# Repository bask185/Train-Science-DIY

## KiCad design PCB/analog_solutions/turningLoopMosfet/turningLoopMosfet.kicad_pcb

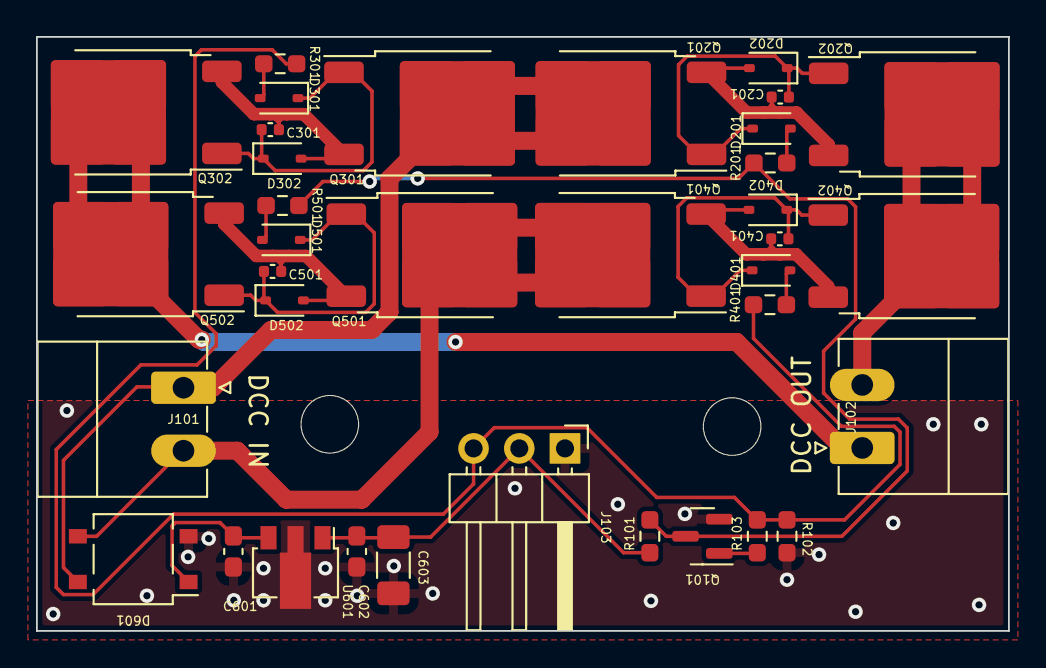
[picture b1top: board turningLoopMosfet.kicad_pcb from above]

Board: 2 copper layers, 54.0 x 33.0 mm, 36 parts (0 on the bottom side), 22 nets.

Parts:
C201, C301, C401, C501: 100nF; C_0402_1005Metric
C601: 330nF; C_0603_1608Metric_Pad1.08x0.95mm_HandSolder
C602: 100nF; C_0603_1608Metric_Pad1.08x0.95mm_HandSolder
C603: 100uF; C_1206_3216Metric_Pad1.33x1.80mm_HandSolder
D201, D202, D301, D302, D401, D402, D501, D502: 1N4148WS; D_SOD-323
D601: MB10S; TO-269AA
J101, J102: Screw_Terminal_01x02; PhoenixContact_MC_1,5_2-G-3.5_1x02_P3.50mm_Horizontal
J103: Conn_01x03_Pin; PinHeader_1x03_P2.54mm_Horizontal
Q101: NPN_TOR; SOT-23
Q201, Q202, Q301, Q302, Q401, Q402, Q501, Q502: MDD50N03D; TO-252-2
R101, R102: 22k; R_0603_smalltext
R103: 2k2; R_0603_smalltext
R201, R301, R401, R501: 100R; R_0603_smalltext
U601: L78L12_SOT89; SOT-89-3

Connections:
+12V: C602.1, C603.1, J103.2, R101.1, U601.1 (OUT)
/DCC_IN_A: D601.3, J101.2, Q401.2 (D), Q501.2 (D)
/DCC_IN_B: D601.4, J101.1, Q201.2 (D), Q301.2 (D)
/DCC_OUT_A: J102.1, Q302.2 (D), Q502.2 (D)
/DCC_OUT_B: J102.2, Q202.2 (D), Q402.2 (D)
/Mosfets2/GATE: Q101.3 (C), R101.2, R201.1, R501.1
/Vo: J103.3, R102.1, R103.2, R301.1, R401.1
GND: C601.2, C602.2, C603.2, D601.2 (-), J103.1, Q101.2 (E), R102.2, U601.2 (GND)
unnamed: D201.2 (A), R201.2
unnamed: C201.2, D201.1 (K), D202.1 (K), Q201.1 (G), Q202.1 (G)
unnamed: C201.1, D202.2 (A), Q201.3 (S), Q202.3 (S)
unnamed: D301.2 (A), R301.2
unnamed: C301.2, D301.1 (K), D302.1 (K), Q301.1 (G), Q302.1 (G)
unnamed: C301.1, D302.2 (A), Q301.3 (S), Q302.3 (S)
unnamed: D401.2 (A), R401.2
unnamed: C401.2, D401.1 (K), D402.1 (K), Q401.1 (G), Q402.1 (G)
unnamed: C401.1, D402.2 (A), Q401.3 (S), Q402.3 (S)
unnamed: D501.2 (A), R501.2
unnamed: C501.2, D501.1 (K), D502.1 (K), Q501.1 (G), Q502.1 (G)
unnamed: C501.1, D502.2 (A), Q501.3 (S), Q502.3 (S)
unnamed: Q101.1 (B), R103.1
VCC: C601.1, D601.1 (+), U601.3 (IN)

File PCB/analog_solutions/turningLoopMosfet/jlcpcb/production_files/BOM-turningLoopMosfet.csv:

Comment,Designator,Footprint,LCSC
100nF,C602,C_0603_1608Metric_Pad1.08x0.95mm_HandSolder,C14663
100uF,C603,C_1206_3216Metric_Pad1.33x1.80mm_HandSolder,C15008
330nF,C601,C_0603_1608Metric_Pad1.08x0.95mm_HandSolder,C1615
1N4148WS,"D201,D202,D301,D302,D401,D402,D501,D502",D_SOD-323,C2128
NPN_TOR,Q101,SOT-23,C2145
100R,"R201,R301,R401,R501",R_0603_smalltext,C22775
MB10S,D601,TO-269AA,C2488
100nF,"C201,C301,C401,C501",C_0402_1005Metric,C307331
22k,"R101,R102",R_0603_smalltext,C31850
2k2,R103,R_0603_smalltext,C4190
MDD50N03D,"Q201,Q202,Q301,Q302,Q401,Q402,Q501,Q502",TO-252-2,C5357578
L78L12_SOT89,U601,SOT-89-3,C75501

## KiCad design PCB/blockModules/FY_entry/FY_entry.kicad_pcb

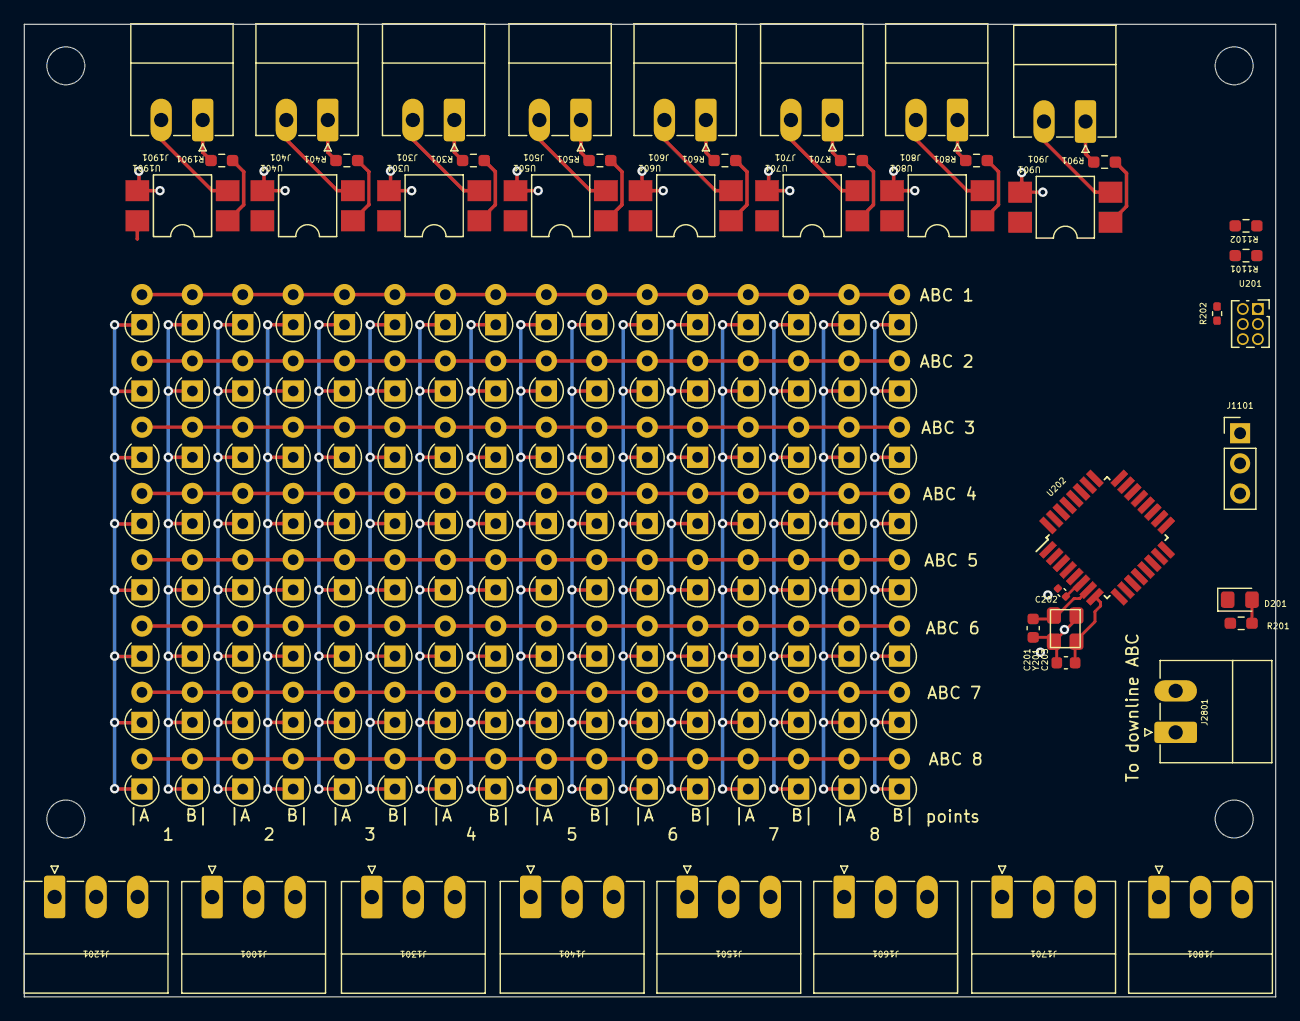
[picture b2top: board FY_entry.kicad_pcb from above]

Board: 2 copper layers, 105.5 x 82.0 mm, 173 parts (0 on the bottom side), 67 nets.

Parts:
C201, C203: 12pF; C_0603_1608Metric
C202: 100nF; C_0402_1005Metric
D201: LED; LED_0805_2012Metric_Pad1.15x1.40mm_HandSolder
D1901, D1902, D1903, D1904, D1905, D1906, D1907, D1908, D1909, D1910, D1911, D1912, D1913, D1914, D1915, D1916, D2101, D2102, D2103, D2104, D2105, D2106, D2107, D2108, D2109, D2110, D2111, D2112, D2113, D2114, D2115, D2116, D2201, D2202, D2203, D2204, D2205, D2206, D2207, D2208, D2209, D2210, D2211, D2212, D2213, D2214, D2215, D2216, D2301, D2302, D2303, D2304, D2305, D2306, D2307, D2308, D2309, D2310, D2311, D2312, D2313, D2314, D2315, D2316, D2401, D2402, D2403, D2404, D2405, D2406, D2407, D2408, D2409, D2410, D2411, D2412, D2413, D2414, D2415, D2416, D2501, D2502, D2503, D2504, D2505, D2506, D2507, D2508, D2509, D2510, D2511, D2512, D2513, D2514, D2515, D2516, D2601, D2602, D2603, D2604, D2605, D2606, D2607, D2608, D2609, D2610, D2611, D2612, D2613, D2614, D2615, D2616, D2701, D2702, D2703, D2704, D2705, D2706, D2707, D2708, D2709, D2710, D2711, D2712, D2713, D2714, D2715, D2716: D; D_A-405_P2.54mm_Vertical_AnodeUp
J301, J401, J501, J601, J701, J801, J901, J1901, J2801: Screw_Terminal_01x02; PhoenixContact_MC_1,5_2-G-3.5_1x02_P3.50mm_Horizontal
J1001, J1201, J1301, J1401, J1501, J1601, J1701, J1801: Screw_Terminal_01x03; PhoenixContact_MC_1,5_3-G-3.5_1x03_P3.50mm_Horizontal
J1101: Conn_01x03; PinHeader_1x03_P2.54mm_Vertical
R201: 6k2; R_0603_1608Metric_Pad0.98x0.95mm_HandSolder
R202: 10k; R_0402_1005Metric_Pad0.72x0.64mm_HandSolder
R301, R401, R501, R601, R701, R801, R901, R1901: 330R; R_0603_smalltext
R1101, R1102: 22k; R_0603_smalltext
U201: HEADER_3x2; PinSocket_2x03_P1.27mm_Vertical
U202: ATmega328-A; TQFP-32_7x7mm_P0.8mm
U301, U401, U501, U601, U701, U801, U901, U1901: EL817S; SMDIP-4_W7.62mm
Y201: Crystal_GND2; crystal_arduino

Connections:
+5V: C202.1, R201.1, R202.1, R1101.2, R1102.1, U201.5, U202.4 (VCC), U202.6 (VCC), U202.18 (AVCC)
/atmega/LED: D201.1 (K), U201.4, U202.17 (PB5)
/atmega/MISO: U201.6, U202.16 (PB4)
/atmega/MOSI: U201.3, U202.15 (PB3)
/atmega/X1: C201.2, U202.7 (XTAL1/PB6), Y201.1
/atmega/X2: C203.2, U202.8 (XTAL2/PB7), Y201.3
/atmega/line1: D2701.2 (A), D2702.2 (A), D2703.2 (A), D2704.2 (A), D2705.2 (A), D2706.2 (A), D2707.2 (A), D2708.2 (A), D2709.2 (A), D2710.2 (A), D2711.2 (A), D2712.2 (A), D2713.2 (A), D2714.2 (A), D2715.2 (A), D2716.2 (A), U202.30 (PD0)
/atmega/line2: D2601.2 (A), D2602.2 (A), D2603.2 (A), D2604.2 (A), D2605.2 (A), D2606.2 (A), D2607.2 (A), D2608.2 (A), D2609.2 (A), D2610.2 (A), D2611.2 (A), D2612.2 (A), D2613.2 (A), D2614.2 (A), D2615.2 (A), D2616.2 (A), U202.31 (PD1)
/atmega/line3: D2501.2 (A), D2502.2 (A), D2503.2 (A), D2504.2 (A), D2505.2 (A), D2506.2 (A), D2507.2 (A), D2508.2 (A), D2509.2 (A), D2510.2 (A), D2511.2 (A), D2512.2 (A), D2513.2 (A), D2514.2 (A), D2515.2 (A), D2516.2 (A), U202.32 (PD2)
/atmega/line4: D2401.2 (A), D2402.2 (A), D2403.2 (A), D2404.2 (A), D2405.2 (A), D2406.2 (A), D2407.2 (A), D2408.2 (A), D2409.2 (A), D2410.2 (A), D2411.2 (A), D2412.2 (A), D2413.2 (A), D2414.2 (A), D2415.2 (A), D2416.2 (A), U202.1 (PD3)
/atmega/line5: D2301.2 (A), D2302.2 (A), D2303.2 (A), D2304.2 (A), D2305.2 (A), D2306.2 (A), D2307.2 (A), D2308.2 (A), D2309.2 (A), D2310.2 (A), D2311.2 (A), D2312.2 (A), D2313.2 (A), D2314.2 (A), D2315.2 (A), D2316.2 (A), U202.2 (PD4)
/atmega/line6: D2201.2 (A), D2202.2 (A), D2203.2 (A), D2204.2 (A), D2205.2 (A), D2206.2 (A), D2207.2 (A), D2208.2 (A), D2209.2 (A), D2210.2 (A), D2211.2 (A), D2212.2 (A), D2213.2 (A), D2214.2 (A), D2215.2 (A), D2216.2 (A), U202.9 (PD5)
/atmega/line7: D1901.2 (A), D1902.2 (A), D1903.2 (A), D1904.2 (A), D1905.2 (A), D1906.2 (A), D1907.2 (A), D1908.2 (A), D1909.2 (A), D1910.2 (A), D1911.2 (A), D1912.2 (A), D1913.2 (A), D1914.2 (A), D1915.2 (A), D1916.2 (A), U202.10 (PD6)
/atmega/line8: D2101.2 (A), D2102.2 (A), D2103.2 (A), D2104.2 (A), D2105.2 (A), D2106.2 (A), D2107.2 (A), D2108.2 (A), D2109.2 (A), D2110.2 (A), D2111.2 (A), D2112.2 (A), D2113.2 (A), D2114.2 (A), D2115.2 (A), D2116.2 (A), U202.11 (PD7)
/atmega/occupied: J2801.2, U202.12 (PB0)
/atmega/occupied1: U202.23 (PC0), U1901.4
/atmega/occupied2: U202.24 (PC1), U401.4
/atmega/occupied3: U202.25 (PC2), U301.4
/atmega/occupied4: U202.26 (PC3), U501.4
/atmega/occupied5: U202.27 (PC4), U601.4
/atmega/occupied6: U202.28 (PC5), U701.4
/atmega/occupied7: R1101.1, U202.19 (ADC6), U801.4
/atmega/occupied8: R1102.2, U202.22 (ADC7), U901.4
/atmega/reset: R202.2, U201.2, U202.29 (~RESET/PC6)
/diodeMatrix/point1A: D1901.1 (K), D2101.1 (K), D2201.1 (K), D2301.1 (K), D2401.1 (K), D2501.1 (K), D2601.1 (K), D2701.1 (K), J1201.1
/diodeMatrix/point1B: D1902.1 (K), D2102.1 (K), D2202.1 (K), D2302.1 (K), D2402.1 (K), D2502.1 (K), D2602.1 (K), D2702.1 (K), J1201.3
/diodeMatrix/point2A: D1903.1 (K), D2103.1 (K), D2203.1 (K), D2303.1 (K), D2403.1 (K), D2503.1 (K), D2603.1 (K), D2703.1 (K), J1001.1
/diodeMatrix/point2B: D1904.1 (K), D2104.1 (K), D2204.1 (K), D2304.1 (K), D2404.1 (K), D2504.1 (K), D2604.1 (K), D2704.1 (K), J1001.3
/diodeMatrix/point3A: D1905.1 (K), D2105.1 (K), D2205.1 (K), D2305.1 (K), D2405.1 (K), D2505.1 (K), D2605.1 (K), D2705.1 (K), J1301.1
/diodeMatrix/point3B: D1906.1 (K), D2106.1 (K), D2206.1 (K), D2306.1 (K), D2406.1 (K), D2506.1 (K), D2606.1 (K), D2706.1 (K), J1301.3
/diodeMatrix/point4A: D1907.1 (K), D2107.1 (K), D2207.1 (K), D2307.1 (K), D2407.1 (K), D2507.1 (K), D2607.1 (K), D2707.1 (K), J1401.1
/diodeMatrix/point4B: D1908.1 (K), D2108.1 (K), D2208.1 (K), D2308.1 (K), D2408.1 (K), D2508.1 (K), D2608.1 (K), D2708.1 (K), J1401.3
/diodeMatrix/point5A: D1909.1 (K), D2109.1 (K), D2209.1 (K), D2309.1 (K), D2409.1 (K), D2509.1 (K), D2609.1 (K), D2709.1 (K), J1501.1
/diodeMatrix/point5B: D1910.1 (K), D2110.1 (K), D2210.1 (K), D2310.1 (K), D2410.1 (K), D2510.1 (K), D2610.1 (K), D2710.1 (K), J1501.3
/diodeMatrix/point6A: D1911.1 (K), D2111.1 (K), D2211.1 (K), D2311.1 (K), D2411.1 (K), D2511.1 (K), D2611.1 (K), D2711.1 (K), J1601.1
/diodeMatrix/point6B: D1912.1 (K), D2112.1 (K), D2212.1 (K), D2312.1 (K), D2412.1 (K), D2512.1 (K), D2612.1 (K), D2712.1 (K), J1601.3
/diodeMatrix/point7A: D1913.1 (K), D2113.1 (K), D2213.1 (K), D2313.1 (K), D2413.1 (K), D2513.1 (K), D2613.1 (K), D2713.1 (K), J1701.1
/diodeMatrix/point7B: D1914.1 (K), D2114.1 (K), D2214.1 (K), D2314.1 (K), D2414.1 (K), D2514.1 (K), D2614.1 (K), D2714.1 (K), J1701.3
/diodeMatrix/point8A: D1915.1 (K), D2115.1 (K), D2215.1 (K), D2315.1 (K), D2415.1 (K), D2515.1 (K), D2615.1 (K), D2715.1 (K), J1801.1
/diodeMatrix/point8B: D1916.1 (K), D2116.1 (K), D2216.1 (K), D2316.1 (K), D2416.1 (K), D2516.1 (K), D2616.1 (K), D2716.1 (K), J1801.3
GND: C201.1, C202.2, C203.1, J1001.2, J1101.2, J1201.2, J1301.2, J1401.2, J1501.2, J1601.2, J1701.2, J1801.2, J2801.1, U201.1, U202.3 (GND), U202.5 (GND), U202.21 (GND), U301.3, U401.3, U501.3, U601.3, U701.3, U801.3, U901.3, U1901.3, Y201.2 (GND), Y201.4 (GND)
unnamed: D201.2 (A), R201.2
unnamed: J301.1, R301.2
unnamed: J301.2, U301.2
unnamed: J401.1, R401.2
unnamed: J401.2, U401.2
unnamed: J501.1, R501.2
unnamed: J501.2, U501.2
unnamed: J601.1, R601.2
unnamed: J601.2, U601.2
unnamed: J701.1, R701.2
unnamed: J701.2, U701.2
unnamed: J801.1, R801.2
unnamed: J801.2, U801.2
unnamed: J901.1, R901.2
unnamed: J901.2, U901.2
unnamed: J1101.1, U202.13 (PB1)
unnamed: J1901.1, R1901.2
unnamed: J1901.2, U1901.2
unnamed: R301.1, U301.1
unnamed: R401.1, U401.1
unnamed: R501.1, U501.1
unnamed: R601.1, U601.1
unnamed: R701.1, U701.1
unnamed: R801.1, U801.1
unnamed: R901.1, U901.1
unnamed: R1901.1, U1901.1

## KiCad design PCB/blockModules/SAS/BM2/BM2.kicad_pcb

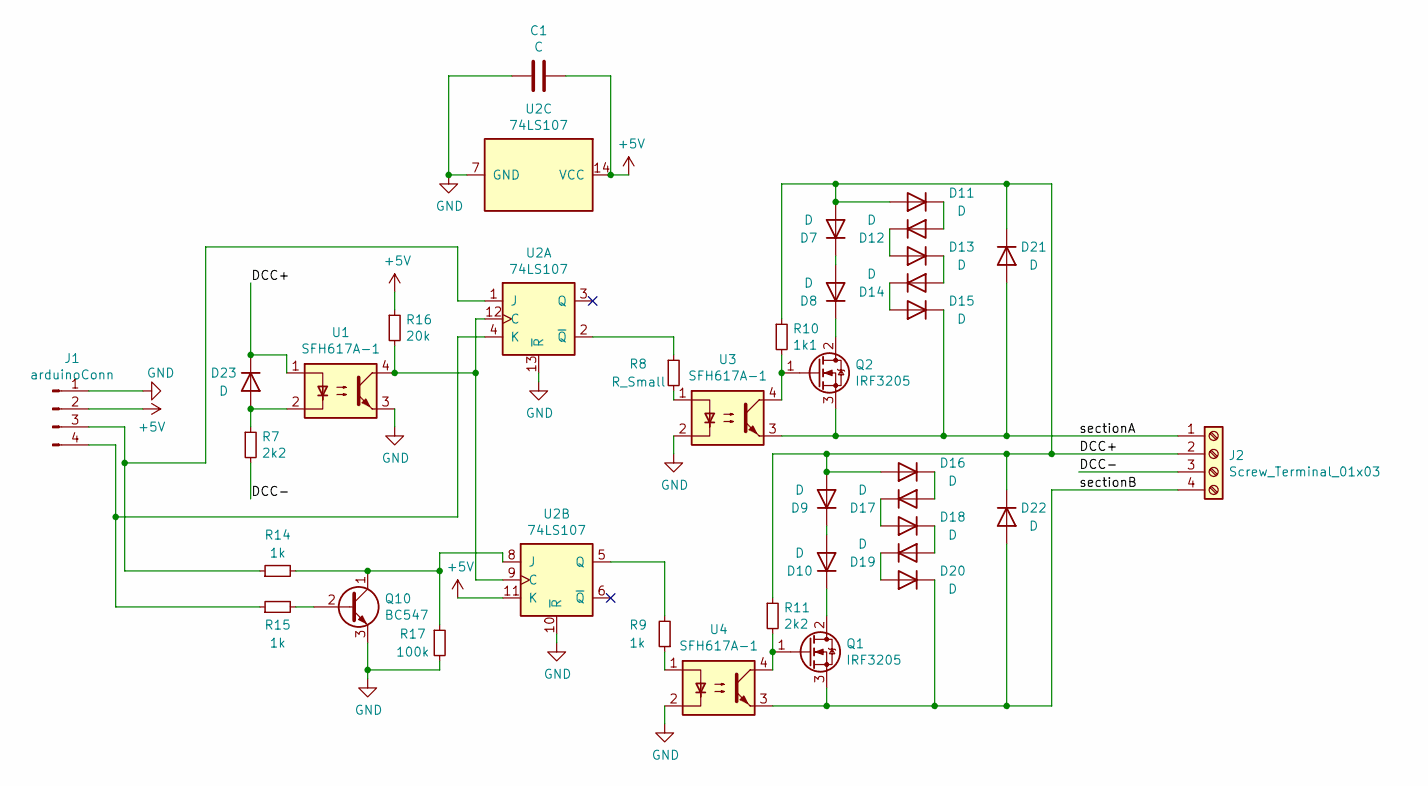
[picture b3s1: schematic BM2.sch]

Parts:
C1: C; C_Disc_D3.0mm_W1.6mm_P2.50mm
D7, D8, D9, D10, D11, D12, D13, D14, D15, D16, D17, D18, D19, D20, D21, D22, D23: D; D_DO-34_SOD68_P7.62mm_Horizontal
J1: arduinoConn; PinHeader_1x04_P2.54mm_Horizontal
J2: Screw_Terminal_01x03; TerminalBlock_bornier-4_P5.08mm
Q1, Q2: IRF3205; TO-220-3_Vertical
Q10: BC547; TO-92_Inline
R7, R11: 2k2; R_Axial_DIN0204_L3.6mm_D1.6mm_P7.62mm_Horizontal
R8: R_Small; R_Axial_DIN0204_L3.6mm_D1.6mm_P7.62mm_Horizontal
R9, R14, R15: 1k; R_Axial_DIN0204_L3.6mm_D1.6mm_P7.62mm_Horizontal
R10: 1k1; R_Axial_DIN0204_L3.6mm_D1.6mm_P7.62mm_Horizontal
R16: 20k; R_Axial_DIN0204_L3.6mm_D1.6mm_P7.62mm_Horizontal
R17: 100k; R_Axial_DIN0204_L3.6mm_D1.6mm_P7.62mm_Horizontal
U1, U3, U4: SFH617A-1; DIP-4_W7.62mm
U2: 74LS107; DIP-14_W7.62mm_LongPads

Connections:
+5V: C1.1, J1.2, R16.1, U2.11 (K), U2.14 (VCC)
/DCC+: D7.2 (A), D9.2 (A), D11.2 (A), D16.2 (A), D21.1 (K), D22.1 (K), D23.1 (K), J2.2, R10.1, R11.1, U1.1
/DCC-: J2.3, R7.2
/sectionA: D15.1 (K), D21.2 (A), J2.1, Q2.3 (S), U3.3
/sectionB: D20.1 (K), D22.2 (A), J2.4, Q1.3 (S), U4.3
GND: C1.2, J1.1, Q10.3 (E), R17.2, U1.3, U2.7 (GND), U2.10 (~R), U2.13 (~R), U3.2, U4.2
unnamed: D7.1 (K), D8.2 (A)
unnamed: D8.1 (K), Q2.2 (D)
unnamed: D10.1 (K), Q1.2 (D)
unnamed: D9.1 (K), D10.2 (A)
unnamed: D11.1 (K), D12.2 (A)
unnamed: D12.1 (K), D13.2 (A)
unnamed: D13.1 (K), D14.2 (A)
unnamed: D14.1 (K), D15.2 (A)
unnamed: D16.1 (K), D17.2 (A)
unnamed: D17.1 (K), D18.2 (A)
unnamed: D18.1 (K), D19.2 (A)
unnamed: D19.1 (K), D20.2 (A)
unnamed: D23.2 (A), R7.1, U1.2
unnamed: J1.3, R14.1, U2.1 (J)
unnamed: J1.4, R15.1, U2.4 (K)
unnamed: Q1.1 (G), R11.2, U4.4
unnamed: Q2.1 (G), R10.2, U3.4
unnamed: Q10.1 (C), R14.2, R17.1, U2.8 (J)
unnamed: Q10.2 (B), R15.2
unnamed: R8.1, U2.2 (~Q)
unnamed: R8.2, U3.1
unnamed: R9.1, U4.1
unnamed: R9.2, U2.5 (Q)
unnamed: R16.2, U1.4, U2.9 (C), U2.12 (C)

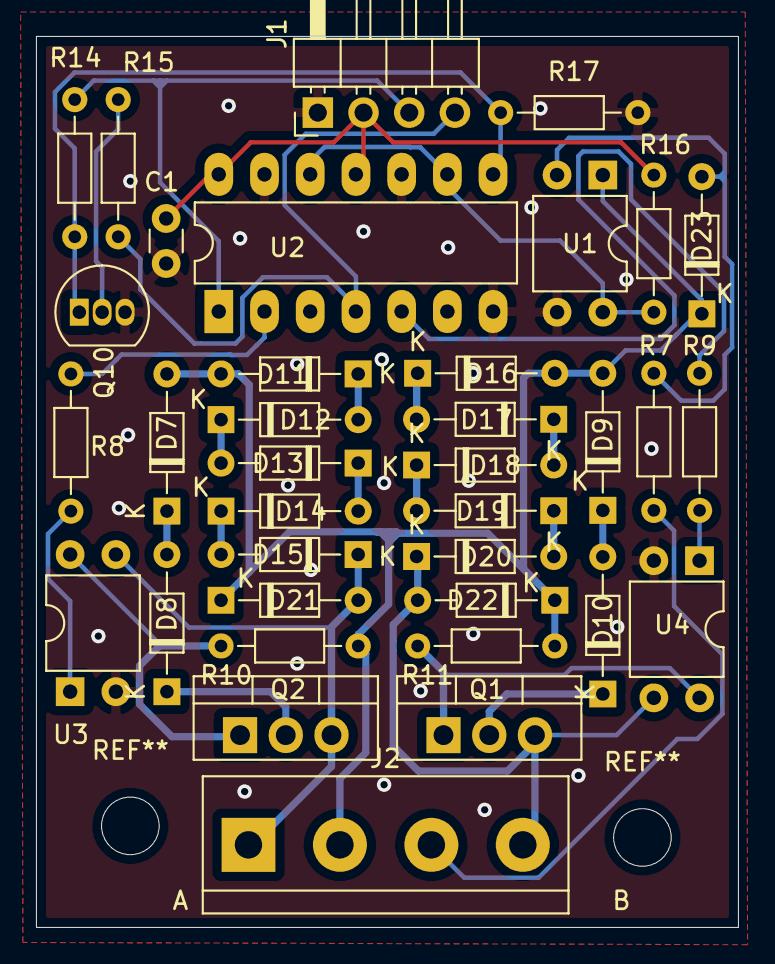
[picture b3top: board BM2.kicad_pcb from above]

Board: 2 copper layers, 39.0 x 49.5 mm, 36 parts (0 on the bottom side), 30 nets.

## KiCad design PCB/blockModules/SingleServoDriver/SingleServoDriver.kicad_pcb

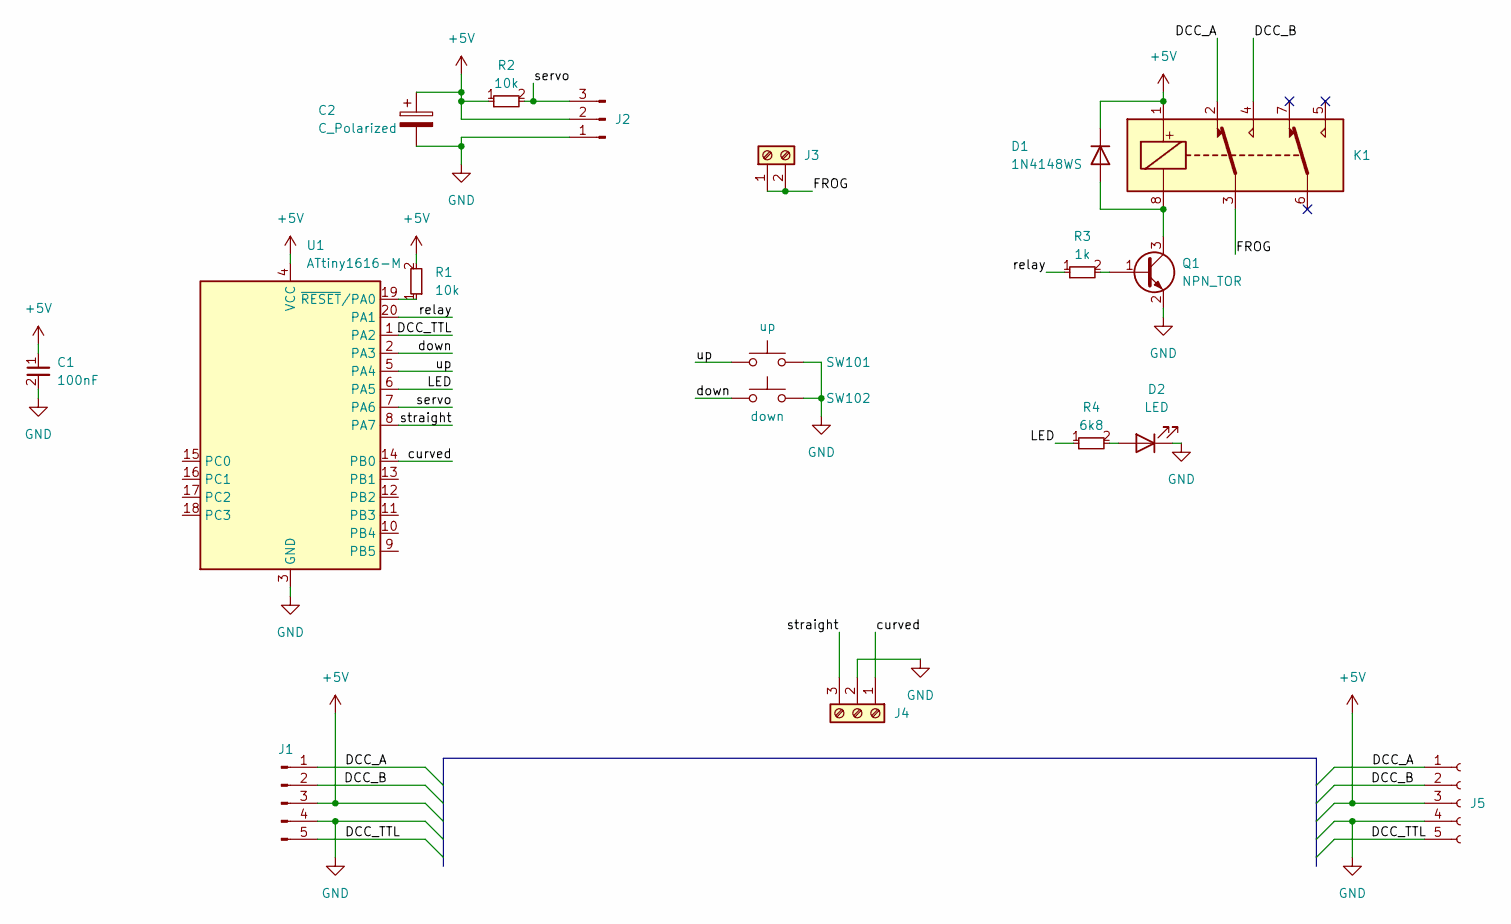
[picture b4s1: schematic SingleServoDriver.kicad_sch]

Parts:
C1: 100nF; C_0402_1005Metric; JLCPCB Part# C307331
C2: C_Polarized; CP_Elec_8x10
D1: 1N4148WS; D_SOD-323; JLCPCB Part# C2128
D2: LED; LED_0805_2012Metric_Pad1.15x1.40mm_HandSolder; JLCPCB Part# C2296
J1: Conn_01x05_Pin; PinHeader_1x05_P2.54mm_Horizontal
J2: Conn_01x03_Pin; PinHeader_1x03_P2.54mm_Vertical
J3: Screw_Terminal_01x02; TerminalBlock_Phoenix_MKDS-1,5-2-5.08_1x02_P5.08mm_Horizont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
J4: Screw_Terminal_01x03; TerminalBlock_Phoenix_MKDS-1,5-3-5.08_1x03_P5.08mm_Horizont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
J5: Conn_01x05_Socket; PinSocket_1x05_P2.54mm_Horizontal
K1: G6K-2F-Y-TR DC5; Relay_DPDT_Omron_G6K-2F-Y; JLCPCB Part# C47190
Q1: NPN_TOR; SOT-23; JLCPCB Part# C2145
R1, R2: 10k; R_0603_smalltext; JLCPCB Part# C25804
R3: 1k; R_0603_smalltext; JLCPCB Part# C21190
R4: 6k8; R_0603_smalltext; JLCPCB Part# C23212
SW101: up; tactile_SMD_6mm; JLCPCB Part# C294567
SW102: down; tactile_SMD_6mm; JLCPCB Part# C294567
U1: ATtiny1616-M; VQFN-20-1EP_3x3mm_P0.4mm_EP1.7x1.7mm; JLCPCB Part# C507118

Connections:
+5V: C1.1, C2.1, D1.1 (K), J1.3, J2.2, J5.3, K1.1, R1.2, R2.1, U1.4 (VCC)
/DCC_A: J1.1, J5.1, K1.2
/DCC_B: J1.2, J5.2, K1.4
/DCC_TTL: J1.5, J5.5, U1.1 (PA2)
/FROG: J3.1, J3.2, K1.3
/LED: R4.1, U1.6 (PA5)
/curved: J4.1, U1.14 (PB0)
/down: SW102.1, U1.2 (PA3)
/relay: R3.1, U1.20 (PA1)
/servo: J2.3, R2.2, U1.7 (PA6)
/straight: J4.3, U1.8 (PA7)
/up: SW101.1, U1.5 (PA4)
GND: C1.2, C2.2, D2.1 (K), J1.4, J2.1, J4.2, J5.4, Q1.2 (E), SW101.2, SW102.2, U1.3 (GND), U1.21 (GND)
unnamed: D1.2 (A), K1.8, Q1.3 (C)
unnamed: D2.2 (A), R4.2
unnamed: Q1.1 (B), R3.2
unnamed: R1.1, U1.19 (~RESET/PA0)

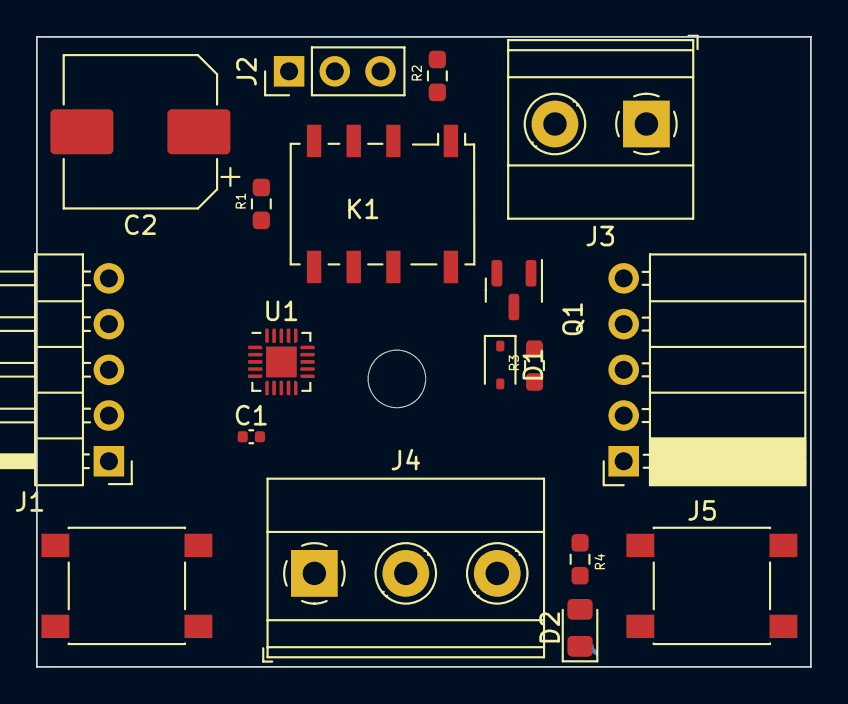
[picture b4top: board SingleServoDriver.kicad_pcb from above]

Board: 2 copper layers, 43.0 x 35.0 mm, 18 parts (0 on the bottom side), 17 nets.

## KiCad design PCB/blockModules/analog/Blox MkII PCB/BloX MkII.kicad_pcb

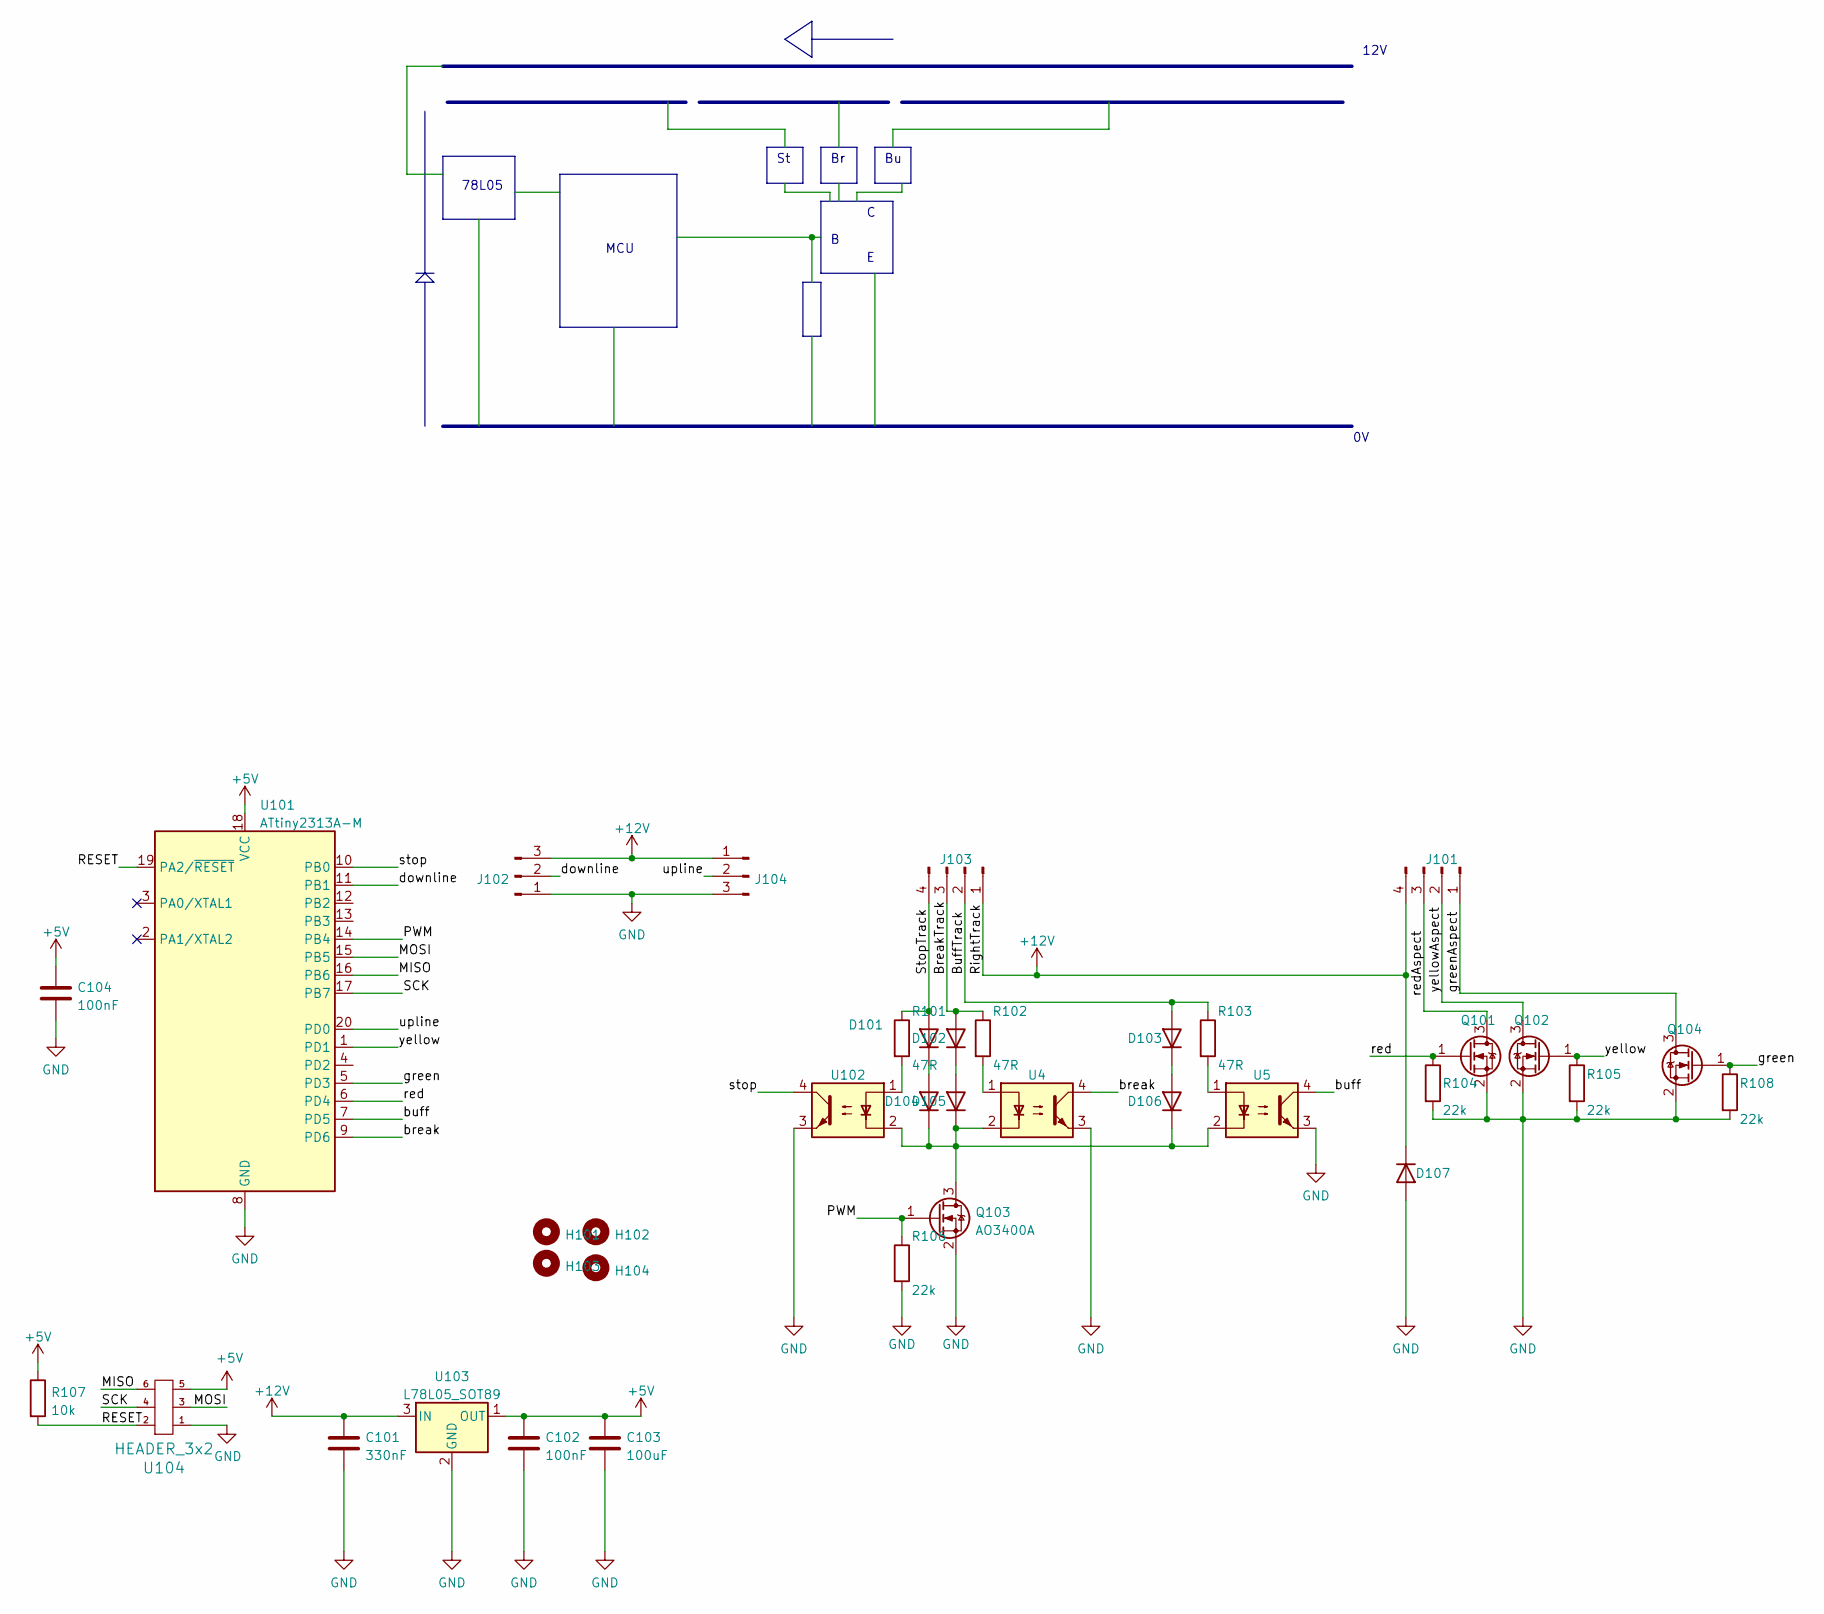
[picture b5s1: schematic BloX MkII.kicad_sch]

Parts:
C101: 330nF; C_0603_1608Metric_Pad1.08x0.95mm_HandSolder; JLCPCB Part# C1615
C102, C104: 100nF; C_0603_1608Metric_Pad1.08x0.95mm_HandSolder; JLCPCB Part# C14663
C103: 100uF; C_1206_3216Metric_Pad1.33x1.80mm_HandSolder; JLCPCB Part# C15008
D101, D102, D103, D104, D105, D106, D107: SM4007; D_SOD-123F; JLCPCB Part# C64898
H101, H102, H103, H104: MountingHole; MountingHole_3.2mm_M3
J101: (no value)
J102, J104: Conn_01x03_Male; PhoenixContact_MC_1,5_3-G-3.81_1x03_P3.81mm_Horizontal
J103: Conn_01x04_Male; PhoenixContact_MC_1,5_4-G-3.81_1x04_P3.81mm_Horizontal
Q101, Q102, Q103, Q104: AO3400A; SOT-23; JLCPCB Part# C20917
R101, R102, R103: 47R; R_0805_2012Metric_Pad1.20x1.40mm_HandSolder; JLCPCB Part# C17714
R104, R105, R106, R108: 22k; R_0805_2012Metric_Pad1.20x1.40mm_HandSolder; JLCPCB Part# C17560
R107: 10k; R_0603_1608Metric_Pad0.98x0.95mm_HandSolder; JLCPCB Part# C25804
U4, U5, U102: SFH617A-3X017T; SMDIP-4_W9.53mm_Clearance8mm
U101: ATtiny2313A-M; MLF-20-1EP_4x4mm_P0.5mm_EP2.6x2.6mm; JLCPCB Part# C185530
U103: L78L05_SOT89; SOT-89-3; JLCPCB Part# C71136
U104: HEADER_3x2; PinSocket_2x03_P1.27mm_Vertical

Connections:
+5V: C102.1, C103.1, C104.1, R107.1, U101.18 (VCC), U103.1 (OUT), U104.5
+12V: C101.1, D107.1 (K), J101.4, J102.3, J103.1, J104.1, U103.3 (IN)
/BreakTrack: D102.2 (A), J103.3, R102.1
/BuffTrack: D103.2 (A), J103.2, R103.1
/MISO: U101.16 (PB6), U104.6
/MOSI: U101.15 (PB5), U104.3
/PWM: Q103.1 (G), R106.1, U101.14 (PB4)
/RESET: R107.2, U101.19 (PA2/~RESET), U104.2
/SCK: U101.17 (PB7), U104.4
/StopTrack: D101.2 (A), J103.4, R101.1
/break: U4.4, U101.9 (PD6)
/buff: U5.4, U101.7 (PD5)
/downline: J102.2, U101.11 (PB1)
/green: Q104.1 (G), R108.1, U101.5 (PD3)
/greenAspect: J101.1, Q104.3 (D)
/red: Q101.1 (G), R104.1, U101.6 (PD4)
/redAspect: J101.3, Q101.3 (D)
/stop: U101.10 (PB0), U102.4
/upline: J104.2, U101.20 (PD0)
/yellow: Q102.1 (G), R105.1, U101.1 (PD1)
/yellowAspect: J101.2, Q102.3 (D)
GND: C101.2, C102.2, C103.2, C104.2, D107.2 (A), J102.1, J104.3, Q101.2 (S), Q102.2 (S), Q103.2 (S), Q104.2 (S), R104.2, R105.2, R106.2, R108.2, U4.3, U5.3, U101.8 (GND), U101.21 (GND), U102.3, U103.2 (GND), U104.1
unnamed: D101.1 (K), D104.2 (A)
unnamed: D102.1 (K), D105.2 (A)
unnamed: D103.1 (K), D106.2 (A)
unnamed: D104.1 (K), D105.1 (K), D106.1 (K), Q103.3 (D), U4.2, U5.2, U102.2
unnamed: R101.2, U102.1
unnamed: R102.2, U4.1
unnamed: R103.2, U5.1

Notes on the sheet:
78L05
MCU
12V

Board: 2 copper layers, 37 parts (0 on the bottom side), 29 nets, no tracks yet.

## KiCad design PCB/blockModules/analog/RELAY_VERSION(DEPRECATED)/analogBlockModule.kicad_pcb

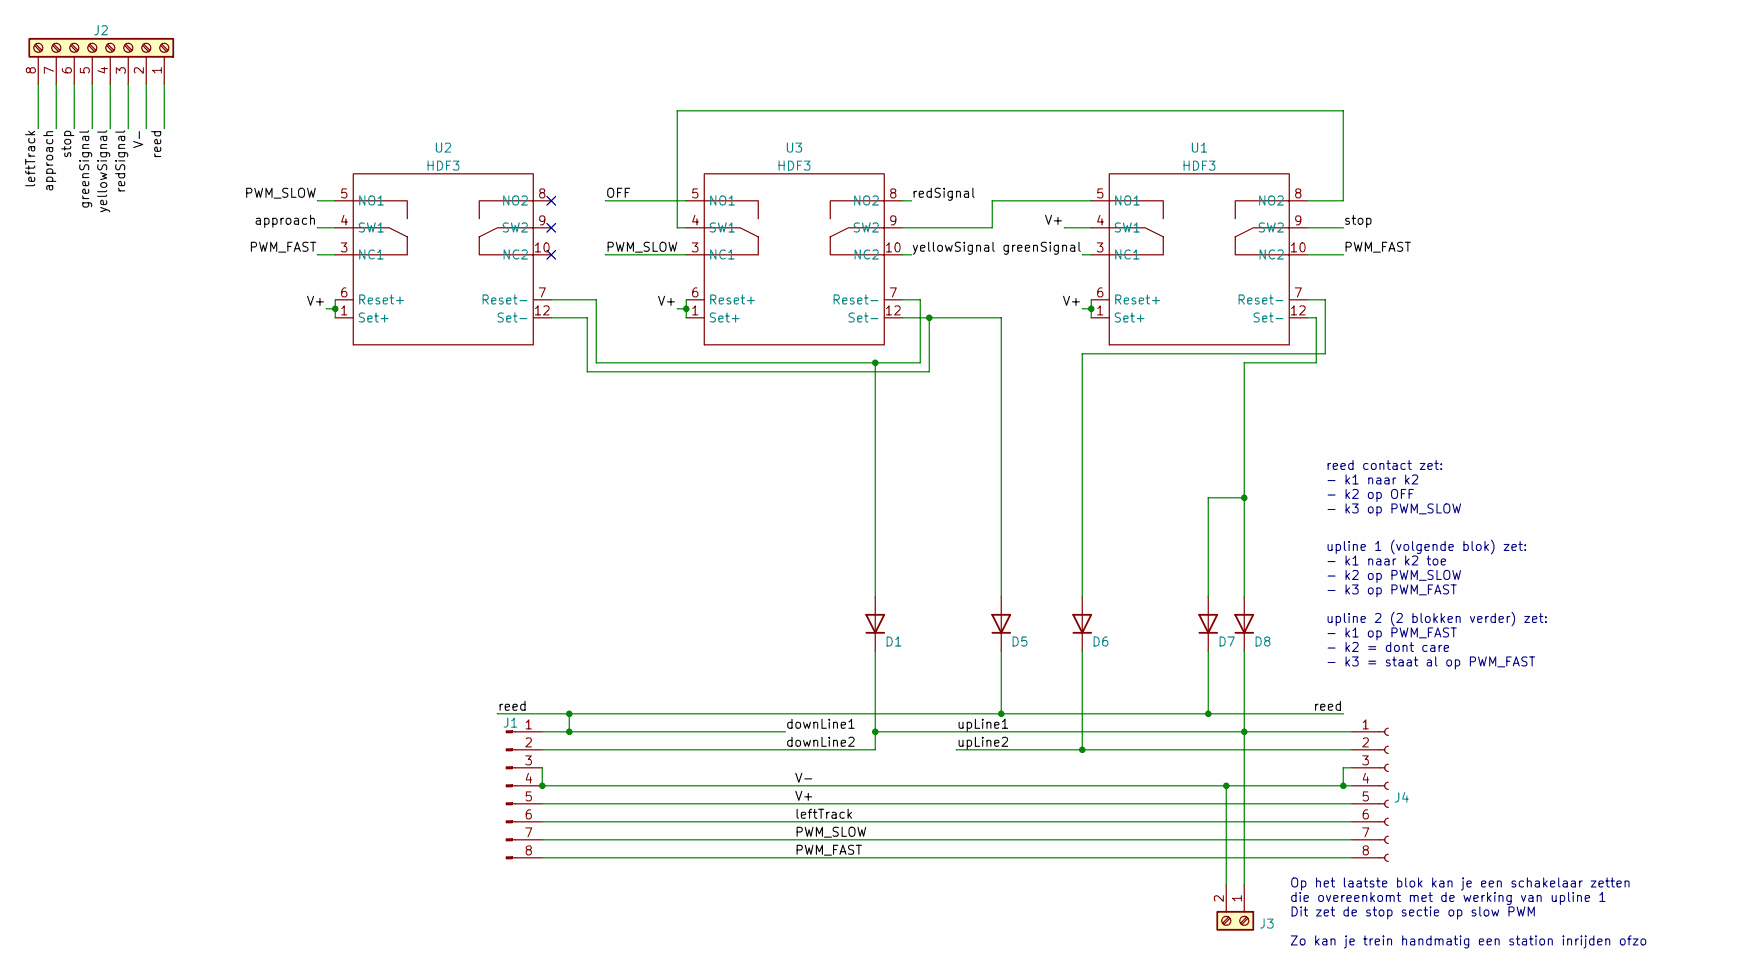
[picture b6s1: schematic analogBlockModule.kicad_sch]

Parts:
D1, D5, D6, D7, D8: D; D_DO-34_SOD68_P7.62mm_Horizontal
J1: Conn_01x08_Male; PinHeader_1x08_P2.54mm_Horizontal
J2: Screw_Terminal_01x08; TerminalBlock_Phoenix_MKDS-1,5-8-5.08_1x08_P5.08mm_Horizont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
J3: Screw_Terminal_01x02; TerminalBlock_Phoenix_MKDS-1,5-2-5.08_1x02_P5.08mm_Horizont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
J4: Conn_01x08_Female; PinSocket_1x08_P2.54mm_Horizontal
U1, U2, U3: HDF3

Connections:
/OFF: U3.5 (NO1)
/PWM_FAST: J1.8, J4.8, U1.10 (NC2), U2.3 (NC1)
/PWM_SLOW: J1.7, J4.7, U2.5 (NO1), U3.3 (NC1)
/V+: J1.5, J4.5, U1.1 (Set+), U1.4 (SW1), U1.6 (Reset+), U2.1 (Set+), U2.6 (Reset+), U3.1 (Set+), U3.6 (Reset+)
/V-: J1.3, J1.4, J2.2, J3.2, J4.3, J4.4
/approach: J2.7, U2.4 (SW1)
/downLine1: D5.1 (K), D7.1 (K), J1.1, J2.1
/downLine2: D1.1 (K), D8.1 (K), J1.2, J3.1, J4.1
/greenSignal: J2.5, U1.3 (NC1)
/leftTrack: J1.6, J2.8, J4.6
/redSignal: J2.3, U3.8 (NO2)
/stop: J2.6, U1.9 (SW2)
/upLine2: D6.1 (K), J4.2
/yellowSignal: J2.4, U3.10 (NC2)
unnamed: D1.2 (A), U2.7 (Reset-), U3.7 (Reset-)
unnamed: D5.2 (A), U2.12 (Set-), U3.12 (Set-)
unnamed: D6.2 (A), U1.7 (Reset-)
unnamed: D7.2 (A), D8.2 (A), U1.12 (Set-)
unnamed: U1.5 (NO1), U3.9 (SW2)
unnamed: U1.8 (NO2), U3.4 (SW1)

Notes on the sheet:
upline 1 (volgende blok) zet: - k1 naar k2 toe - k2 op PWM_SLOW - k3 op PWM_FAST
Op het laatste blok kan je een schakelaar zetten die overeenkomt met de werking van upline 1 Dit zet de stop sectie op slow PWM Zo kan je trein handmatig een station inrijden ofzo
reed contact zet: - k1 naar k2 - k2 op OFF - k3 op PWM_SLOW
upline 2 (2 blokken verder) zet: - k1 op PWM_FAST - k2 = dont care - k3 = staat al op PWM_FAST

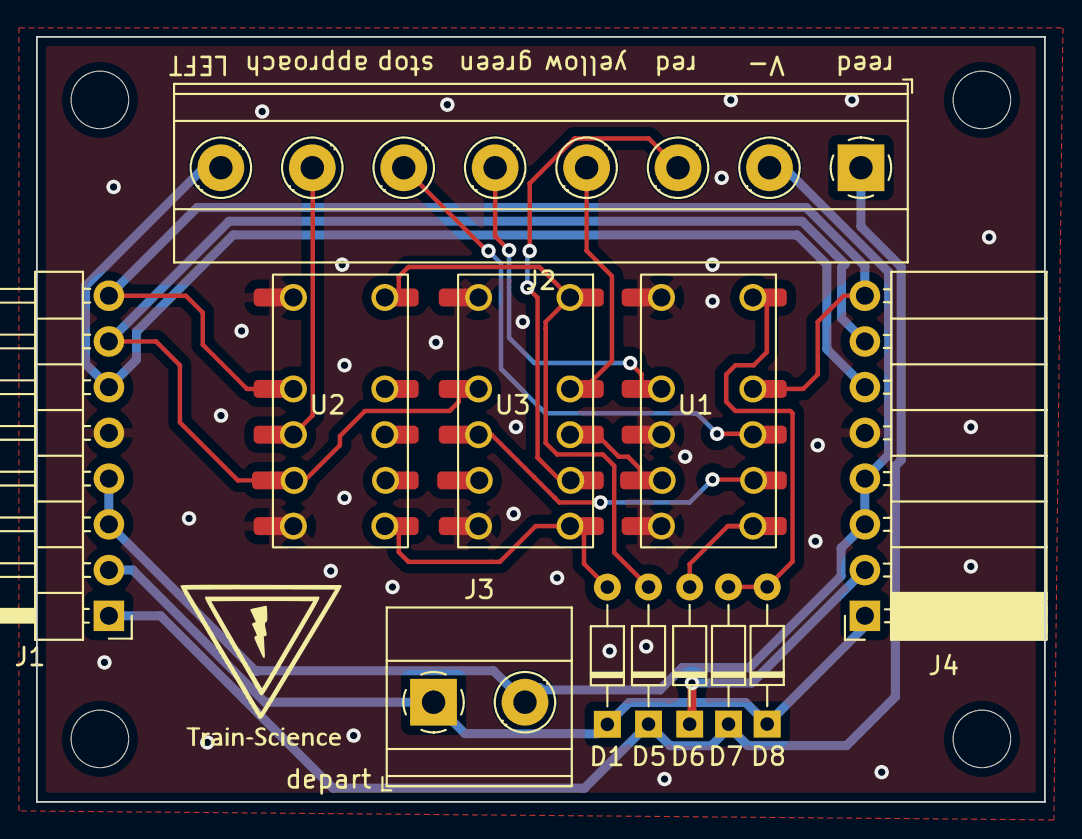
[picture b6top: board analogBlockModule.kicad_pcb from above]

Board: 2 copper layers, 56.0 x 42.5 mm, 12 parts (0 on the bottom side), 19 nets.
